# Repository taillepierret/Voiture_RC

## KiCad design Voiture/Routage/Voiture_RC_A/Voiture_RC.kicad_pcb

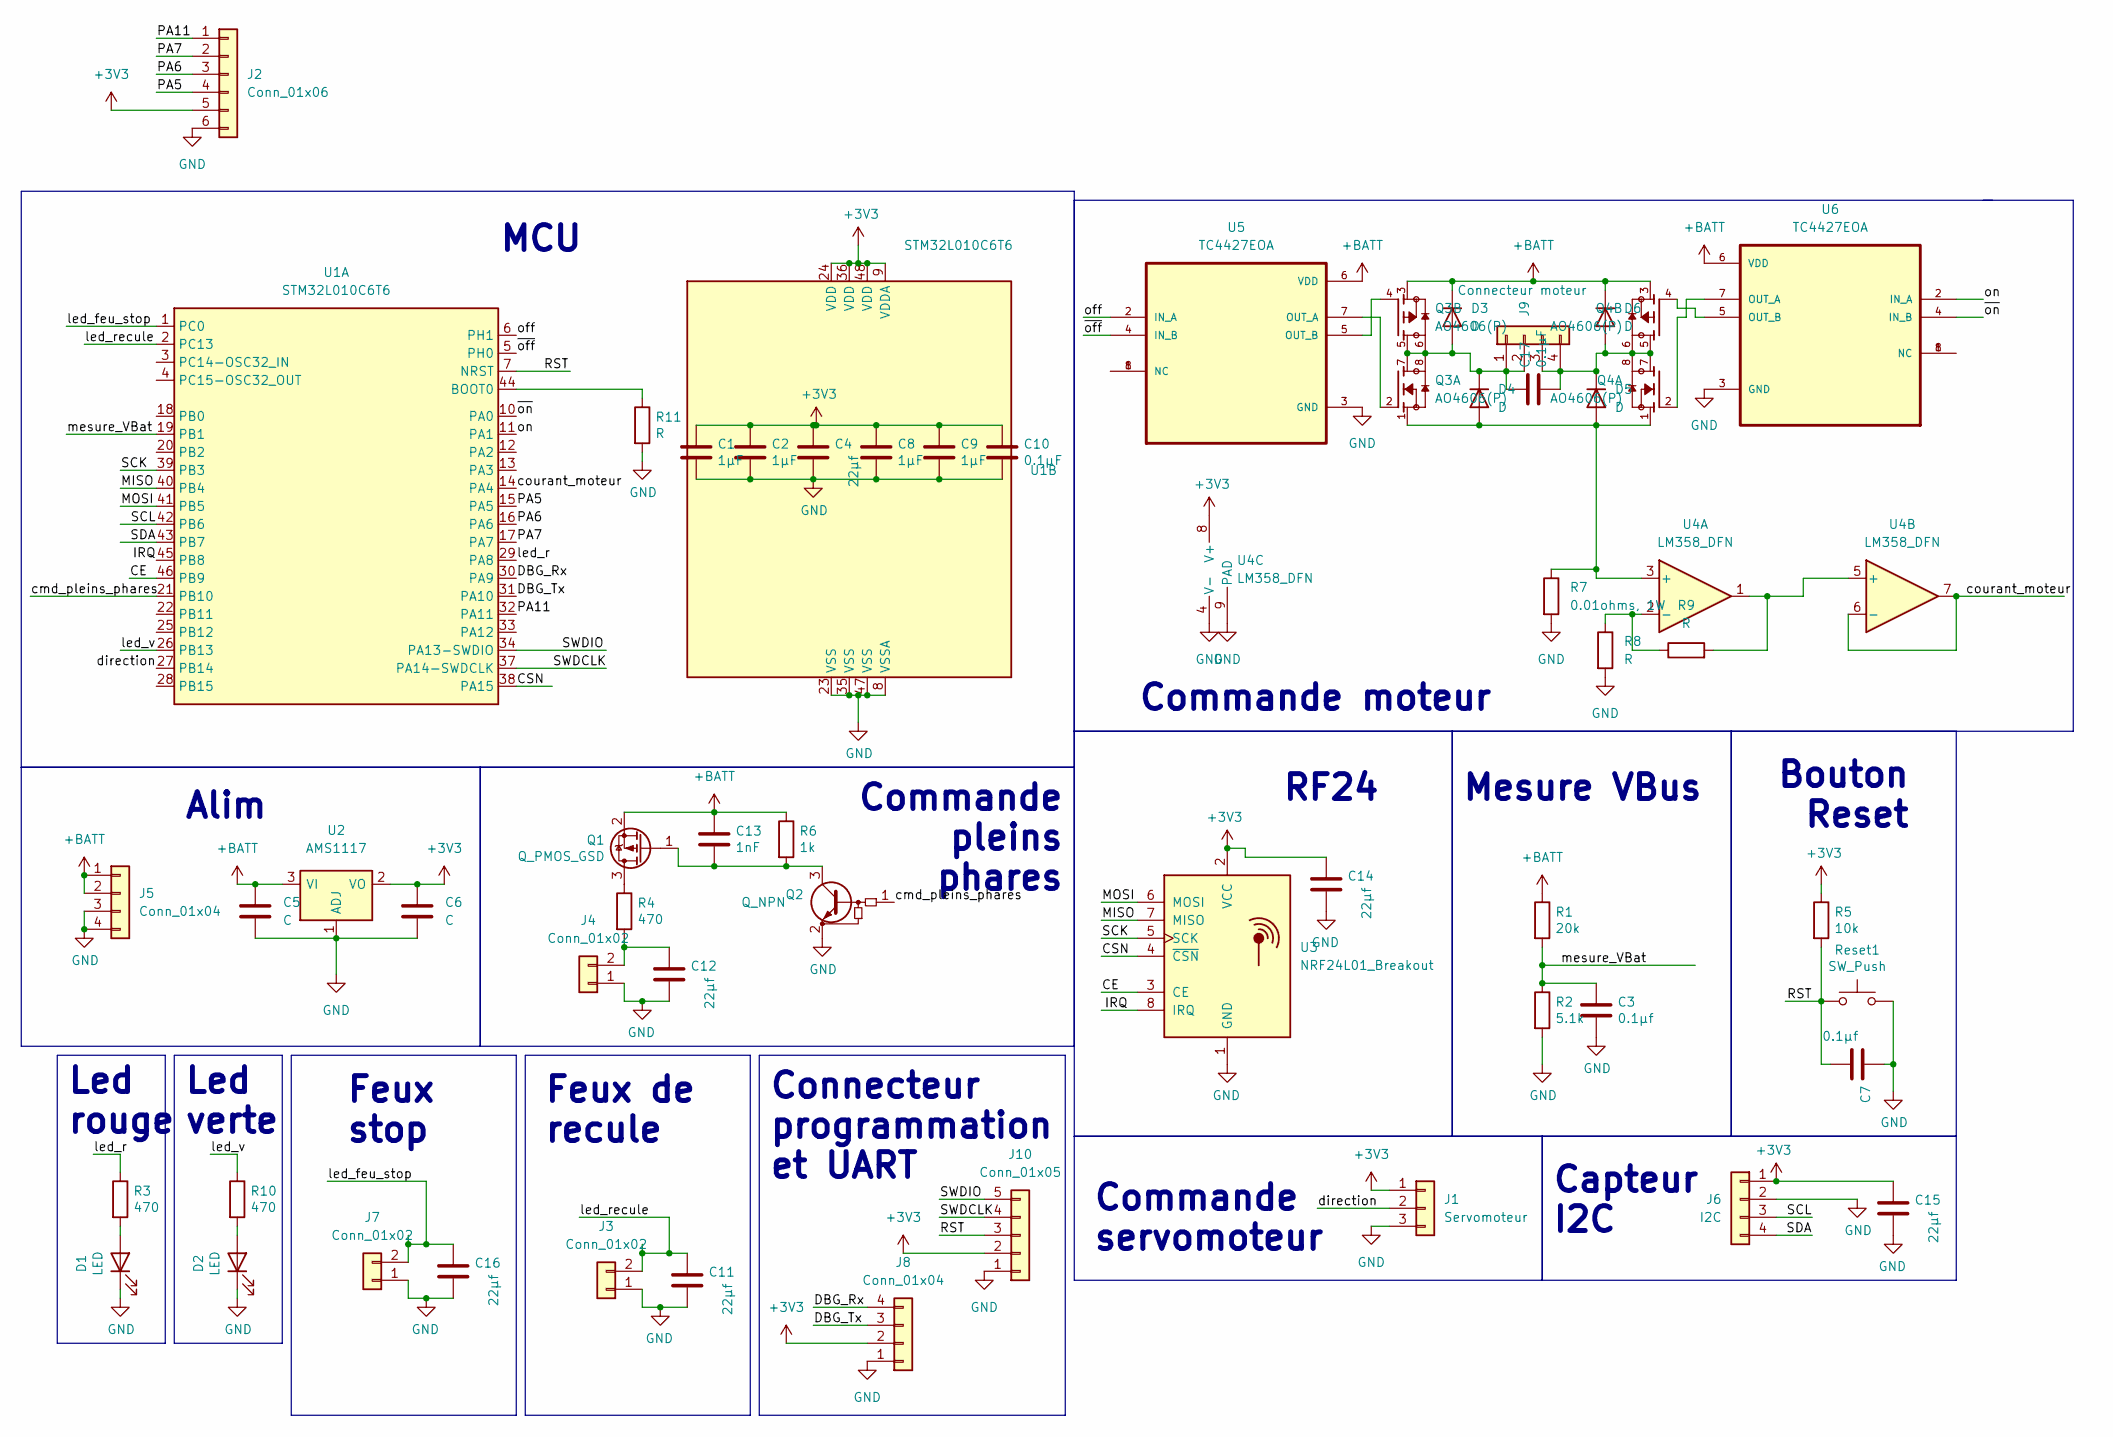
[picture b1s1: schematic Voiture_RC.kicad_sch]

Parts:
C1, C2, C8, C9: 1µF; C_0805_2012Metric
C3, C7: 0.1µf; C_0805_2012Metric
C4, C11, C12, C14, C15, C16: 22µf; C_0805_2012Metric
C5, C6: C; C_0805_2012Metric
C10, C17: 0.1µF; C_0805_2012Metric
C13: 1nF; C_0805_2012Metric
D1, D2: LED; LED_0603_1608Metric
D3, D4, D5, D6: D; D_0603_1608Metric
J1: Servomoteur; PinHeader_1x03_P2.54mm_Vertical
J2: Conn_01x06; PinHeader_1x06_P2.54mm_Vertical
J3, J4, J7: Conn_01x02; PinHeader_1x02_P2.54mm_Vertical
J5: Conn_01x04; PinHeader_1x04_P2.54mm_Vertical
J6: I2C; PinHeader_1x04_P2.54mm_Vertical
J8: Conn_01x04; JST_EH_B4B-EH-A_1x04_P2.50mm_Vertical
J9: Connecteur moteur; PinHeader_1x04_P2.54mm_Vertical
J10: Conn_01x05; JST_EH_B5B-EH-A_1x05_P2.50mm_Vertical
Q1: Q_PMOS_GSD; SOT-23
Q2: Q_NPN; SOT-23
Q3, Q4: AO4606(P); AO4606
R1: 20k; R_0603_1608Metric
R2: 5.1k; R_0603_1608Metric
R3, R4, R10: 470; R_0603_1608Metric
R5: 10k; R_0603_1608Metric
R6: 1k; R_0603_1608Metric
R7: 0.01ohms, 1W; R_1206_3216Metric_Pad1.30x1.75mm_HandSolder
R8, R9, R11: R; R_0603_1608Metric
Reset1: SW_Push; SW_SPST_CK_RS282G05A3
U1: STM32L010C6T6; QFP50P900X900X160-48N
U2: AMS1117; SOT-223-3_TabPin2
U3: NRF24L01_Breakout; nRF24L01_Breakout
U4: LM358_DFN; SOP-8_3.9x4.9mm_P1.27mm
U5, U6: TC4427EOA; SOIC127P599X175-8N

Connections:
+3V3: C1.1, C2.1, C4.1, C6.1, C8.1, C9.1, C10.1, C14.1, C15.1, J1.1, J2.5, J6.1, J8.2, J10.2, R5.1, U1.9 (VDDA), U1.24 (VDD), U1.36 (VDD), U1.48 (VDD), U2.2 (VO), U3.2 (VCC), U4.8 (V+)
+BATT: C5.1, C13.1, D3.1 (K), D6.1 (K), J5.1, J5.2, Q1.2 (S), Q3.3, Q4.3, R1.1, R6.1, U2.3 (VI), U5.6 (VDD), U6.6 (VDD)
/CE: U1.46 (PB9), U3.3 (CE)
/CSN: U1.38 (PA15), U3.4 (~CSN)
/DBG_Rx: J8.4, U1.30 (PA9)
/DBG_Tx: J8.3, U1.31 (PA10)
/IRQ: U1.45 (PB8), U3.8 (IRQ)
/MISO: U1.40 (PB4), U3.7 (MISO)
/MOSI: U1.41 (PB5), U3.6 (MOSI)
/PA5: J2.4, U1.15 (PA5)
/PA6: J2.3, U1.16 (PA6)
/PA7: J2.2, U1.17 (PA7)
/PA11: J2.1, U1.32 (PA11)
/RST: C7.2, J10.3, R5.2, Reset1.1, U1.7 (NRST)
/SCK: U1.39 (PB3), U3.5 (SCK)
/SCL: J6.3, U1.42 (PB6)
/SDA: J6.4, U1.43 (PB7)
/SWDCLK: J10.4, U1.37 (PA14-SWDCLK)
/SWDIO: J10.5, U1.34 (PA13-SWDIO)
/cmd_pleins_phares: Q2.1 (B), U1.21 (PB10)
/courant_moteur: U1.14 (PA4), U4.6 (-), U4.7
/direction: J1.2, U1.27 (PB14)
/led_feu_stop: C16.1, J7.2, U1.1 (PC0)
/led_r: R3.1, U1.29 (PA8)
/led_recule: C11.1, J3.2, U1.2 (PC13)
/led_v: R10.1, U1.26 (PB13)
/mesure_VBat: C3.1, R1.2, R2.1, U1.19 (PB1)
/off: U1.6 (PH1), U5.2 (IN_A)
/on: U1.11 (PA1), U6.2 (IN_A)
/~off: U1.5 (PH0), U5.4 (IN_B)
/~on: U1.10 (PA0), U6.4 (IN_B)
GND: C1.2, C2.2, C3.2, C4.2, C5.2, C6.2, C7.1, C8.2, C9.2, C10.2, C11.2, C12.2, C14.2, C15.2, C16.2, D1.1 (K), D2.1 (K), J1.3, J2.6, J3.1, J4.1, J5.3, J5.4, J6.2, J7.1, J8.1, J10.1, Q2.2 (E), R2.2, R7.2, R8.2, R11.2, Reset1.2, U1.8 (VSSA), U1.23 (VSS), U1.35 (VSS), U1.47 (VSS), U2.1 (ADJ), U3.1 (GND), U4.4 (V-), U4.9 (PAD), U5.3 (GND), U6.3 (GND)
unnamed: C12.1, J4.2, R4.2
unnamed: C13.2, Q1.1 (G), Q2.3 (C), R6.2
unnamed: D1.2 (A), R3.2
unnamed: D2.2 (A), R10.2
unnamed: C17.1, D3.2 (A), D4.1 (K), J9.1, J9.2, Q3.5, Q3.6, Q3.7, Q3.8
unnamed: C17.2, D5.1 (K), D6.2 (A), J9.3, J9.4, Q4.5, Q4.6, Q4.7, Q4.8
unnamed: Q1.3 (D), R4.1
unnamed: D4.2 (A), D5.2 (A), Q3.1, Q4.1, R7.1, U4.3 (+)
unnamed: Q4.2, U6.7 (OUT_A)
unnamed: Q4.4, U6.5 (OUT_B)
unnamed: R8.1, R9.1, U4.2 (-)
unnamed: R9.2, U4.1, U4.5 (+)
unnamed: R11.1, U1.44 (BOOT0)
unnamed: U5.1 (NC), U5.8 (NC)
unnamed: Q3.4, U5.5 (OUT_B)
unnamed: Q3.2, U5.7 (OUT_A)
unnamed: U6.1 (NC), U6.8 (NC)

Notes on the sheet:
Feux de recule
MCU
Alim
Bouton Reset
RF24
Led rouge
Connecteur programmation et UART
Commande moteur
Feux stop
Commande pleins phares
Mesure VBus
Commande servomoteur
Led verte
Capteur I2C

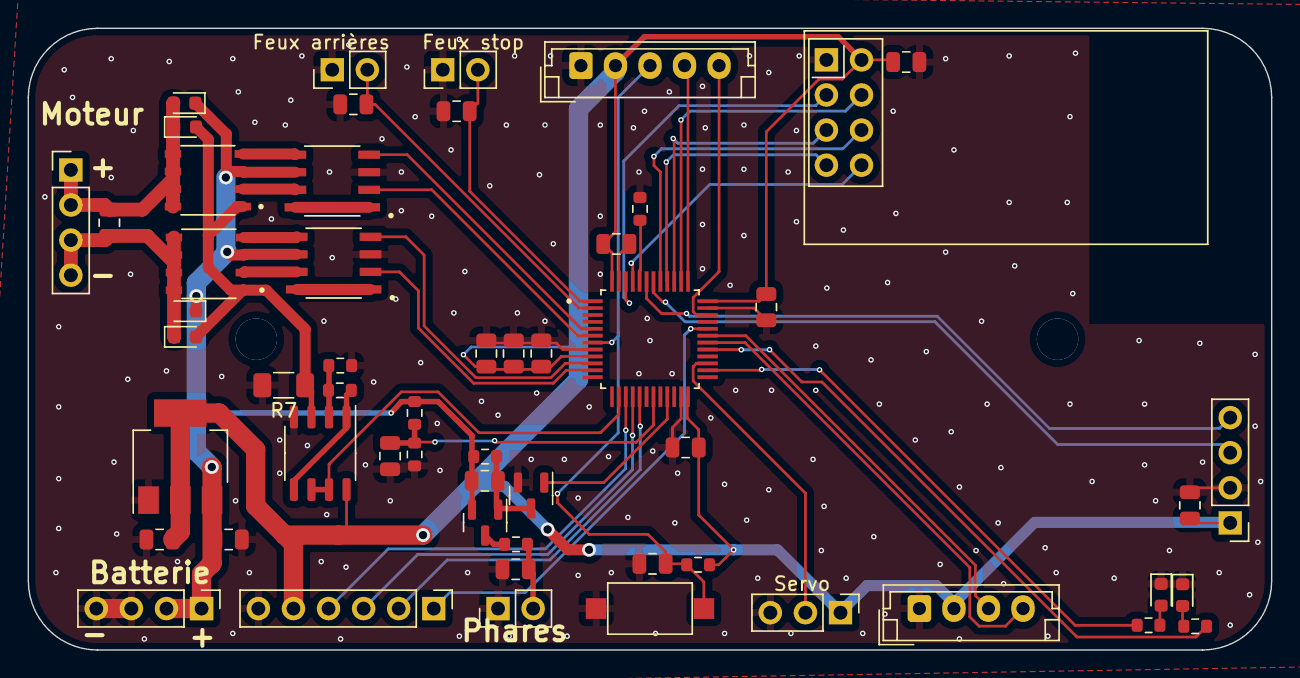
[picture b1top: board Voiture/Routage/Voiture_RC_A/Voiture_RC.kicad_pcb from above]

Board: 2 copper layers, 90.0 x 45.0 mm, 55 parts (0 on the bottom side), 49 nets.

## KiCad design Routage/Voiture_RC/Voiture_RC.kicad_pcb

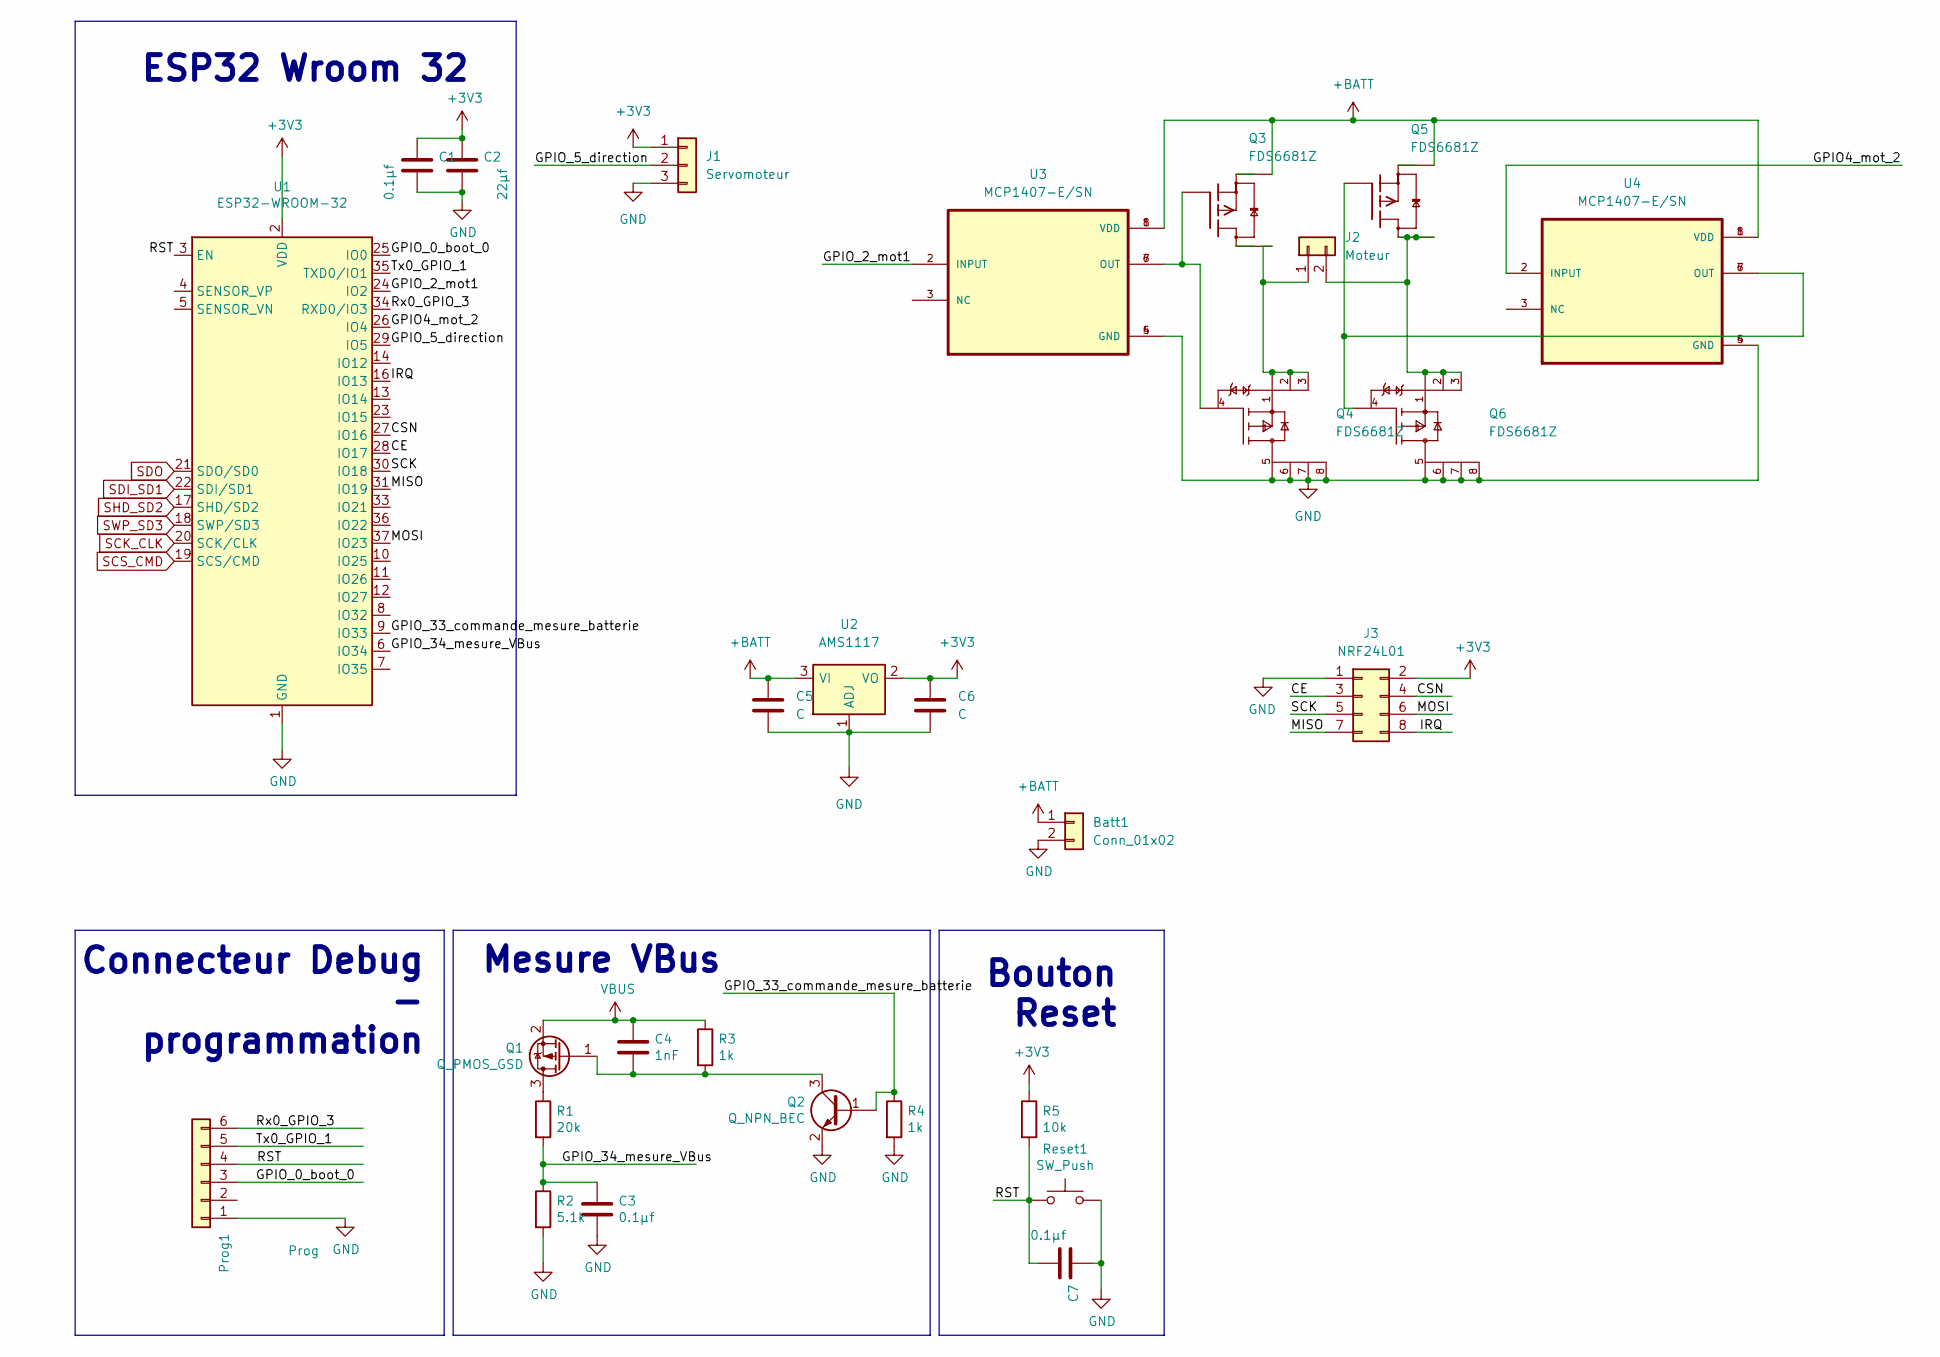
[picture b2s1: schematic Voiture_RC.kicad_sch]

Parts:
Batt1: Conn_01x02; PinHeader_1x02_P2.54mm_Vertical
C1, C3, C7: 0.1µf; C_0603_1608Metric
C2: 22µf; C_0603_1608Metric
C4: 1nF; C_0603_1608Metric
C5, C6: C; C_0603_1608Metric
J1: Servomoteur; PinHeader_1x03_P2.54mm_Vertical
J2: Moteur; PinHeader_1x02_P2.54mm_Vertical
J3: NRF24L01; nRF24L01_Breakout
Prog1: Prog; JST_XH_B6B-XH-AM_1x06_P2.50mm_Vertical
Q1: Q_PMOS_GSD; SOT-23
Q2: Q_NPN_BEC; SOT-23
Q3, Q5: FDS6681Z; SOP-8_3.76x4.96mm_P1.27mm
Q4, Q6: FDS6681Z; SOP-8_3.76x4.96mm_P1.27mm; mouser part number 512-FDS6681Z; digikey description MOSFET P-CH 30V 20A 8-SO
R1: 20k; R_0603_1608Metric
R2: 5.1k; R_0603_1608Metric
R3, R4: 1k; R_0603_1608Metric
R5: 10k; R_0603_1608Metric
Reset1: SW_Push; SW_SPST_CK_RS282G05A3
U1: ESP32-WROOM-32
U2: AMS1117; SOT-223-3_TabPin2
U3, U4: MCP1407-E/SN; SOP-8_3.76x4.96mm_P1.27mm

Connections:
+3V3: C1.1, C2.1, C6.1, J1.1, J3.2, R5.1, U1.2 (VDD), U2.2 (VO)
+BATT: Batt1.1, C5.1, Q3.3, Q5.3, U2.3 (VI), U3.1 (VDD), U3.8 (VDD), U4.1 (VDD), U4.8 (VDD)
/CE: J3.3, U1.28 (IO17)
/CSN: J3.4, U1.27 (IO16)
/GPIO4_mot_2: U1.26 (IO4), U4.2 (INPUT)
/GPIO_0_boot_0: Prog1.3, U1.25 (IO0)
/GPIO_2_mot1: U1.24 (IO2), U3.2 (INPUT)
/GPIO_5_direction: J1.2, U1.29 (IO5)
/GPIO_33_commande_mesure_batterie: Q2.1 (B), R4.1, U1.9 (IO33)
/GPIO_34_mesure_VBus: C3.1, R1.2, R2.1, U1.6 (IO34)
/IRQ: J3.8, U1.16 (IO13)
/MISO: J3.7, U1.31 (IO19)
/MOSI: J3.6, U1.37 (IO23)
/RST: C7.2, Prog1.4, R5.2, Reset1.1, U1.3 (EN)
/Rx0_GPIO_3: Prog1.6, U1.34 (RXD0/IO3)
/SCK: J3.5, U1.30 (IO18)
/Tx0_GPIO_1: Prog1.5, U1.35 (TXD0/IO1)
GND: Batt1.2, C1.2, C2.2, C3.2, C5.2, C6.2, C7.1, J1.3, J3.1, Prog1.1, Q2.2 (E), Q4.5 (D), Q4.6 (D), Q4.7 (D), Q4.8 (D), Q6.5 (D), Q6.6 (D), Q6.7 (D), Q6.8 (D), R2.2, R4.2, Reset1.2, U1.1 (GND), U1.15 (GND), U1.38 (GND), U1.39 (GND), U2.1 (ADJ), U3.4 (GND), U3.5 (GND), U4.4 (GND), U4.5 (GND)
unnamed: C4.2, Q1.1 (G), Q2.3 (C), R3.2
unnamed: J2.1, Q3.8, Q4.1 (S), Q4.2 (S), Q4.3 (S)
unnamed: J2.2, Q5.6, Q5.7, Q5.8, Q6.1 (S), Q6.2 (S), Q6.3 (S)
unnamed: Q1.3 (D), R1.1
unnamed: Q3.1, Q3.2
unnamed: Q3.4, Q4.4 (G), U3.6 (OUT), U3.7 (OUT)
unnamed: Q3.6, Q3.7
unnamed: Q5.1, Q5.2
unnamed: Q5.4, Q6.4 (G), U4.6 (OUT), U4.7 (OUT)
SCK_CLK: U1.20 (SCK/CLK)
SCS_CMD: U1.19 (SCS/CMD)
SDI_SD1: U1.22 (SDI/SD1)
SDO: U1.21 (SDO/SD0)
SHD_SD2: U1.17 (SHD/SD2)
SWP_SD3: U1.18 (SWP/SD3)
VBUS: C4.1, Q1.2 (S), R3.1

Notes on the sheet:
Connecteur Debug - programmation
Bouton Reset
ESP32 Wroom 32
Mesure VBus

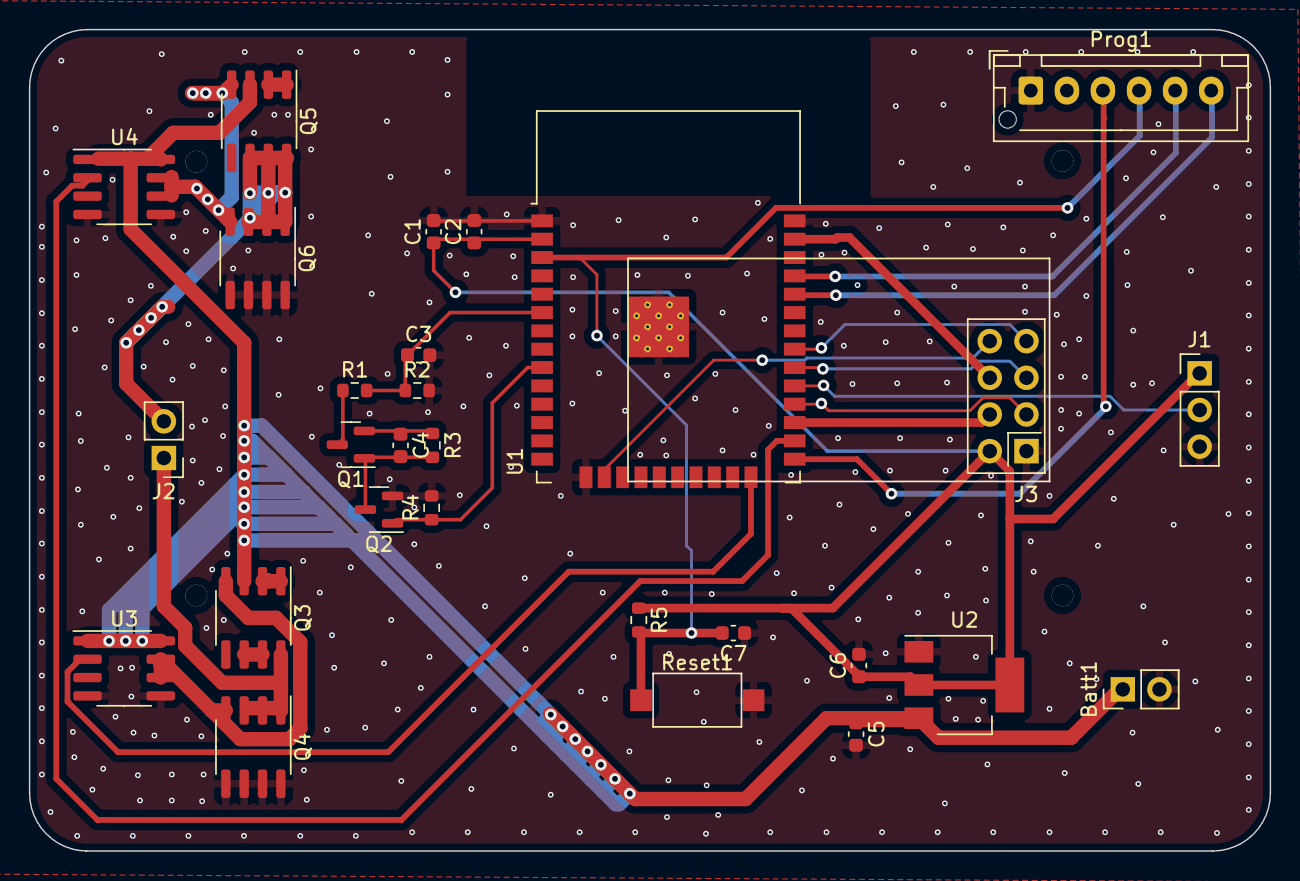
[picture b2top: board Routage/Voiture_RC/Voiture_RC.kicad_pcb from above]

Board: 2 copper layers, 86.0 x 56.9 mm, 28 parts (0 on the bottom side), 28 nets.

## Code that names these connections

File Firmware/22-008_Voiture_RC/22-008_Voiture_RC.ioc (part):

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Mcu.Name=STM32L010C6Tx
Mcu.Package=LQFP48
Mcu.UserName=STM32L010C6Tx
PA0.GPIOParameters=GPIO_PuPd,GPIO_Label
PA0.GPIO_Label=onb
PA0.GPIO_PuPd=GPIO_PULLDOWN
PA0.Signal=S_TIM2_CH1
PA1.GPIOParameters=GPIO_PuPd,GPIO_Label
PA1.GPIO_Label=on
PA1.GPIO_PuPd=GPIO_PULLDOWN
PA1.Signal=S_TIM2_CH2
PA10.Mode=Asynchronous
PA10.Signal=USART2_RX
PA15.GPIOParameters=GPIO_Label
PA15.GPIO_Label=CSN
PA15.Signal=GPIO_Output
PA2.Mode=Timestamp enabled
PA2.Signal=RTC_TS
PA4.GPIOParameters=GPIO_Label
PA4.GPIO_Label=Courant_moteur
PA4.Mode=IN4
PA4.Signal=ADC_IN4
PA8.GPIOParameters=PinState,GPIO_Label
PA8.GPIO_Label=led_r
PA8.PinState=GPIO_PIN_SET
PA8.Signal=GPIO_Output
PA9.Mode=Asynchronous
PA9.Signal=USART2_TX
PB1.GPIOParameters=GPIO_Label
PB1.GPIO_Label=Tension_batterie
PB1.Mode=IN9
PB1.Signal=ADC_IN9
PB10.GPIOParameters=GPIO_Label
PB10.GPIO_Label=cmd_pleins_phares
PB10.Signal=GPIO_Output
PB13.GPIOParameters=PinState,GPIO_Label
PB13.GPIO_Label=led_v
PB13.PinState=GPIO_PIN_SET
PB13.Signal=GPIO_Output
PB14.GPIOParameters=GPIO_Label
PB14.GPIO_Label=direction
PB14.Signal=GPIO_Output
PB3.Mode=Full_Duplex_Master
PB3.Signal=SPI1_SCK
PB4.Mode=Full_Duplex_Master
PB4.Signal=SPI1_MISO
PB5.Mode=Full_Duplex_Master
PB5.Signal=SPI1_MOSI
PB6.Mode=I2C
PB6.Signal=I2C1_SCL
PB7.Mode=I2C
PB7.Signal=I2C1_SDA
PB8.GPIOParameters=GPIO_Label
PB8.GPIO_Label=IRQ
PB8.Signal=GPIO_Output
PB9.GPIOParameters=GPIO_Label
PB9.GPIO_Label=CE
PB9.Signal=GPIO_Output
PH0-OSC_IN.GPIOParameters=GPIO_PuPd,GPIO_Label
PH0-OSC_IN.GPIO_Label=offb
PH0-OSC_IN.GPIO_PuPd=GPIO_PULLDOWN
PH0-OSC_IN.Signal=GPIO_Output
PH1-OSC_OUT.GPIOParameters=GPIO_PuPd,GPIO_Label
PH1-OSC_OUT.GPIO_Label=off
PH1-OSC_OUT.GPIO_PuPd=GPIO_PULLDOWN
PH1-OSC_OUT.Signal=GPIO_Output
RCC.HSE_VALUE=8000000
RCC.SYSCLKFreq_VALUE=2097000
board=custom

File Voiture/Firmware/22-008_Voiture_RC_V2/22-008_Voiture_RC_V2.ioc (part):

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Mcu.Name=STM32L010C6Tx
Mcu.Package=LQFP48
Mcu.UserName=STM32L010C6Tx
PA0.GPIOParameters=GPIO_Label
PA0.GPIO_Label=ON_B_EN
PA0.Signal=S_TIM2_CH1
PA1.GPIOParameters=GPIO_Label
PA1.GPIO_Label=ON_EN
PA1.Signal=S_TIM2_CH2
PA10.Mode=Asynchronous
PA10.Signal=USART2_RX
PA13.Mode=Serial_Wire
PA13.Signal=SYS_SWDIO
PA14.Mode=Serial_Wire
PA14.Signal=SYS_SWCLK
PA15.GPIOParameters=GPIO_Label
PA15.GPIO_Label=CSN_EN
PA15.Signal=GPIO_Output
PA4.GPIOParameters=GPIO_Label
PA4.GPIO_Label=COURANT_MOTEUR_EN
PA4.Mode=IN4
PA4.Signal=ADC_IN4
PA8.GPIOParameters=GPIO_Label
PA8.GPIO_Label=LED_R_EN
PA8.Signal=GPIO_Output
PA9.Mode=Asynchronous
PA9.Signal=USART2_TX
PB1.GPIOParameters=GPIO_Label
PB1.GPIO_Label=TENSION_BATTERIE_EN
PB1.Mode=IN9
PB1.Signal=ADC_IN9
PB10.GPIOParameters=GPIO_Label
PB10.GPIO_Label=CMD_PLEINS_PHARES_EN
PB10.Signal=GPIO_Output
PB13.GPIOParameters=GPIO_Speed,GPIO_Label
PB13.GPIO_Label=LED_V_EN
PB13.GPIO_Speed=GPIO_SPEED_FREQ_HIGH
PB13.Signal=GPIO_Output
PB14.GPIOParameters=GPIO_Label
PB14.GPIO_Label=DIRECTION_EN
PB14.Signal=GPIO_Output
PB3.GPIOParameters=GPIO_Label
PB3.GPIO_Label=SCK_EN
PB3.Mode=Full_Duplex_Master
PB3.Signal=SPI1_SCK
PB4.GPIOParameters=GPIO_Label
PB4.GPIO_Label=MISO_EN
PB4.Mode=Full_Duplex_Master
PB4.Signal=SPI1_MISO
PB5.GPIOParameters=GPIO_Label
PB5.GPIO_Label=MOSI_EN
PB5.Mode=Full_Duplex_Master
PB5.Signal=SPI1_MOSI
PB6.Mode=I2C
PB6.Signal=I2C1_SCL
PB7.Mode=I2C
PB7.Signal=I2C1_SDA
PB9.GPIOParameters=GPIO_Label
PB9.GPIO_Label=CE_EN
PB9.Signal=GPIO_Output
PH0-OSC_IN.GPIOParameters=GPIO_Label
PH0-OSC_IN.GPIO_Label=OFF_B_EN
PH0-OSC_IN.Signal=GPIO_Output
PH1-OSC_OUT.GPIOParameters=GPIO_Label
PH1-OSC_OUT.GPIO_Label=OFF_EN
PH1-OSC_OUT.Signal=GPIO_Output
RCC.HSE_VALUE=8000000
RCC.SYSCLKFreq_VALUE=2097000
board=custom

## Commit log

2023-06-06 Version 1 du Hard
2023-06-06 Modification des mosfets avec les vrais symbols
2023-09-19 creation du projet stm32
2023-09-26 Ne fonctionne pas ... je peux lire puis ecrire mais pas relire
2023-09-26 Semble focntionner mais pas tester completement
2023-09-26 Début, non testé
2023-09-27 avancées mais ne compile pas encore
2023-09-27 idem
2023-09-30 Fait mais pas testé
2023-09-30 ajout de code pour Rx et Tx radio
2023-10-01 Compile et la com SPI fonctionne la com radio n'est pas testee
2024-02-26 Sauvegarde
2024-07-07 creation de la V2 avec vscode, qui compile, televerse mais ne debug pas
2024-07-08 ajout state machine de l'envoi + creation de plusieurs fichiers + debut de la création des trames
2024-07-09 ajout du process de decodage de trame(pas fini) + ajout de la lib nrf24l01 + debut state machine RX radio
2024-07-10 ajout du decodage de trame et de l'envoie de ACK, il faut encore faire la focntion de decodage de trame autre que ack
2024-07-15 suppression des fichiers et ajout des sous modules
2024-07-15 réarangement d'architecture, ca compile !
2024-07-21 ajout d'un commentaire TODO
2024-08-04 ménage et import de code propre
2024-08-04 bug fix
2024-08-04 improvements
